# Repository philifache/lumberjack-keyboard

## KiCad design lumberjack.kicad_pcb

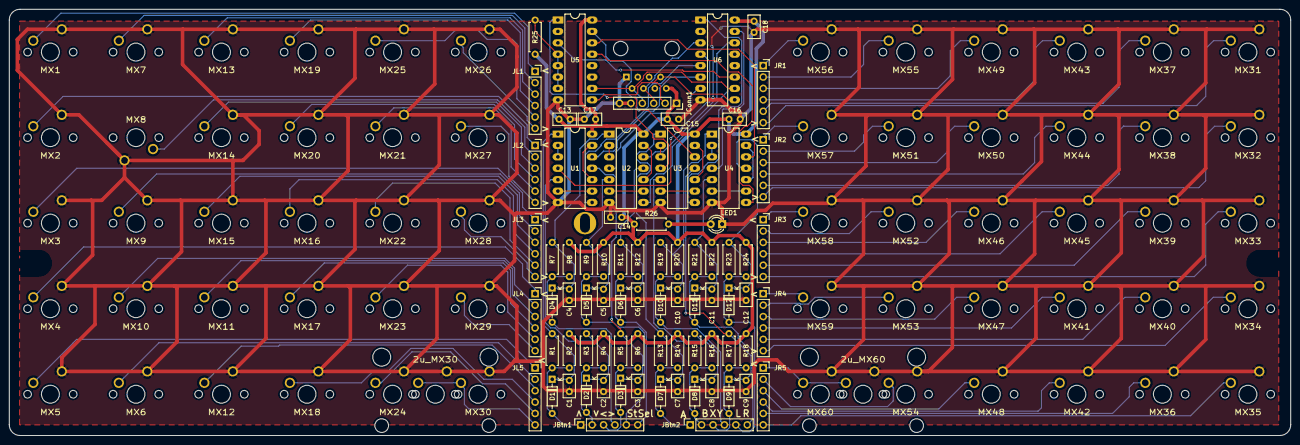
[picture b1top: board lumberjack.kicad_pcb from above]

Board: 2 copper layers, 285.4 x 94.9 mm, 142 parts (1 on the bottom side), 116 nets.

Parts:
2u_MX30, 2u_MX60: SW_Push; MX_PCB_200B
C1, C2, C3, C4, C5, C6, C7, C8, C9, C10, C11, C12, C13, C14, C15, C16, C17, C18: 0.1uF; C_Disc_D5.0mm_W2.5mm_P2.50mm
D1, D2, D3, D4, D5, D6, D7, D8, D9, D10, D11, D12: 1N4148; D_DO-35_SOD27_P7.62mm_Horizontal
H5, H6, H7: M2; MountingSlot_M2
J1: RJ45; RJ45_Amphenol_54602-x08_Horizontal
JBtn1, JBtn2: Conn_01x06_Male; PinSocket_1x06_P2.54mm_Vertical
JConn1: Conn_01x06_Male; PinSocket_1x06_P2.54mm_Vertical
JL1, JL2, JL3, JL4, JL5: Conn_01x06_Male; PinSocket_1x06_P2.54mm_Vertical
JR1, JR2, JR3, JR4, JR5: Conn_01x06_Male; PinSocket_1x06_P2.54mm_Vertical
LED1: RED; LED_D3.0mm
MX1, MX2, MX3, MX4, MX5, MX6, MX7, MX8, MX9, MX10, MX11, MX12, MX13, MX14, MX15, MX16, MX17, MX18, MX19, MX20, MX21, MX22, MX23, MX24, MX25, MX26, MX27, MX28, MX29, MX30, MX31, MX32, MX33, MX34, MX35, MX36, MX37, MX38, MX39, MX40, MX41, MX42, MX43, MX44, MX45, MX46, MX47, MX48, MX49, MX50, MX51, MX52, MX53, MX54, MX55, MX56, MX57, MX58, MX59, MX60: SW_Push; MX
R1, R3, R5, R7, R9, R11, R13, R15, R17, R19, R21, R23: 46.4k; R_Axial_DIN0207_L6.3mm_D2.5mm_P7.62mm_Horizontal
R2, R4, R6, R8, R10, R12, R14, R16, R18, R20, R22, R24, R25: 205k; R_Axial_DIN0207_L6.3mm_D2.5mm_P7.62mm_Horizontal
R26: 470; R_Axial_DIN0207_L6.3mm_D2.5mm_P7.62mm_Horizontal
U1, U2, U3, U4: 74HC14; DIP-14_W7.62mm_LongPads
U5, U6: 4021; DIP-16_W7.62mm_LongPads

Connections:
+5V: C13.1, C14.1, C15.1, C16.1, C17.1, C18.1, J1.8, JConn1.1, R2.1, R4.1, R6.1, R8.1, R10.1, R12.1, R14.1, R16.1, R18.1, R20.1, R22.1, R24.1, R25.1, R26.1, U1.14, U2.14, U3.14, U4.14, U5.16, U6.16
/BtnA: D7.2, JBtn2.1, R13.1, R14.2
/BtnADebounced: U3.4, U5.1
/BtnB: D8.2, JBtn2.2, R15.1, R16.2
/BtnBDebounced: U3.8, U6.1
/BtnDown: D2.2, JBtn1.2, R3.1, R4.2
/BtnDownDebounced: U1.8, U6.5
/BtnL: D12.2, JBtn2.5, R23.1, R24.2
/BtnLDebounced: U4.12, U5.14
/BtnLeft: D3.2, JBtn1.3, R5.1, R6.2
/BtnLeftDebounced: U1.12, U6.6
/BtnRDebounced: U4.8, U5.13
/BtnRight: D4.2, JBtn1.4, R7.1, R8.2
/BtnRightDebounced: U2.4, U6.7
/BtnSelect: D6.2, JBtn1.6, R11.1, R12.2
/BtnSelectDebounced: U2.12, U6.14
/BtnStart: D5.2, JBtn1.5, R9.1, R10.2
/BtnStartDebounced: U2.8, U6.13
/BtnUp: D1.2, JBtn1.1, R1.1, R2.2
/BtnUpDebounced: U1.4, U6.4
/BtnX: D9.2, JBtn2.3, R17.1, R18.2
/BtnXDebounced: U3.12, U5.15
/BtnY: D10.2, JBtn2.4, R19.1, R20.2
/BtnYDebounced: U4.4, U6.15
/L1.1: JL1.1, MX1.2
/L1.2: JL1.2, MX7.2
/L1.3: JL1.3, MX13.2
/L1.4: JL1.4, MX19.2
/L1.5: JL1.5, MX25.2
/L1.6: JL1.6, MX26.2
/L2.1: JL2.1, MX2.2
/L2.2: JL2.2, MX8.2
/L2.3: JL2.3, MX14.2
/L2.4: JL2.4, MX20.2
/L2.5: JL2.5, MX21.2
/L2.6: JL2.6, MX27.2
/L3.1: JL3.1, MX3.2
/L3.2: JL3.2, MX9.2
/L3.3: JL3.3, MX15.2
/L3.4: JL3.4, MX16.2
/L3.5: JL3.5, MX22.2
/L3.6: JL3.6, MX28.2
/L4.1: JL4.1, MX4.2
/L4.2: JL4.2, MX10.2
/L4.3: JL4.3, MX11.2
/L4.4: JL4.4, MX17.2
/L4.5: JL4.5, MX23.2
/L4.6: JL4.6, MX29.2
/L5.1: JL5.1, MX5.2
/L5.2: JL5.2, MX6.2
/L5.3: JL5.3, MX12.2
/L5.4: JL5.4, MX18.2
/L5.5: JL5.5, MX24.2
/L5.6: 2u_MX30.2, JL5.6, MX30.2
/R1.1: JR1.1, MX56.2
/R1.2: JR1.2, MX55.2
/R1.3: JR1.3, MX49.2
/R1.4: JR1.4, MX43.2
/R1.5: JR1.5, MX37.2
/R1.6: JR1.6, MX31.2
/R2.1: JR2.1, MX57.2
/R2.2: JR2.2, MX51.2
/R2.3: JR2.3, MX50.2
/R2.4: JR2.4, MX44.2
/R2.5: JR2.5, MX38.2
/R2.6: JR2.6, MX32.2
/R3.1: JR3.1, MX58.2
/R3.2: JR3.2, MX52.2
/R3.3: JR3.3, MX46.2
/R3.4: JR3.4, MX45.2
/R3.5: JR3.5, MX39.2
/R3.6: JR3.6, MX33.2
/R4.1: JR4.1, MX59.2
/R4.2: JR4.2, MX53.2
/R4.3: JR4.3, MX47.2
/R4.4: JR4.4, MX41.2
/R4.5: JR4.5, MX40.2
/R4.6: JR4.6, MX34.2
/R5.1: 2u_MX60.2, JR5.1, MX60.2
/R5.2: JR5.2, MX54.2
/R5.3: JR5.3, MX48.2
/R5.4: JR5.4, MX42.2
/R5.5: JR5.5, MX36.2
/R5.6: JR5.6, MX35.2
/RtnR: D11.2, JBtn2.6, R21.1, R22.2
/clock: J1.2, JConn1.4, U5.10, U6.10
/data: J1.4, JConn1.3, U6.3
/reset: J1.7, JConn1.2, U5.9, U6.9
GND: 2u_MX30.1, 2u_MX60.1, C1.2, C2.2, C3.2, C4.2, C5.2, C6.2, C7.2, C8.2, C9.2, C10.2, C11.2, C12.2, C13.2, C14.2, C15.2, C16.2, C17.2, C18.2, J1.1, JConn1.5, JConn1.6, LED1.1, MX1.1, MX2.1, MX3.1, MX4.1, MX5.1, MX6.1, MX7.1, MX8.1, MX9.1, MX10.1, MX11.1, MX12.1, MX13.1, MX14.1, MX15.1, MX16.1, MX17.1, MX18.1, MX19.1, MX20.1, MX21.1, MX22.1, MX23.1, MX24.1, MX25.1, MX26.1, MX27.1, MX28.1, MX29.1, MX30.1, MX31.1, MX32.1, MX33.1, MX34.1, MX35.1, MX36.1, MX37.1, MX38.1, MX39.1, MX40.1, MX41.1, MX42.1, MX43.1, MX44.1, MX45.1, MX46.1, MX47.1, MX48.1, MX49.1, MX50.1, MX51.1, MX52.1, MX53.1, MX54.1, MX55.1, MX56.1, MX57.1, MX58.1, MX59.1, MX60.1, U1.7, U2.7, U3.7, U4.7, U5.8, U6.8
unnamed: C1.1, D1.1, R1.2, U1.1
unnamed: C2.1, D2.1, R3.2, U1.5
unnamed: C3.1, D3.1, R5.2, U1.11
unnamed: C4.1, D4.1, R7.2, U2.1
unnamed: C5.1, D5.1, R9.2, U2.5
unnamed: C6.1, D6.1, R11.2, U2.11
unnamed: C7.1, D7.1, R13.2, U3.1
unnamed: C8.1, D8.1, R15.2, U3.5
unnamed: C9.1, D9.1, R17.2, U3.11
unnamed: C10.1, D10.1, R19.2, U4.1
unnamed: C11.1, D11.1, R21.2, U4.5
unnamed: C12.1, D12.1, R23.2, U4.11
unnamed: LED1.2, R26.2
unnamed: R25.2, U5.4, U5.5, U5.6, U5.7
unnamed: U1.2, U1.3
unnamed: U1.6, U1.9
unnamed: U1.10, U1.13
unnamed: U2.2, U2.3
unnamed: U2.6, U2.9
unnamed: U2.10, U2.13
unnamed: U3.2, U3.3
unnamed: U3.6, U3.9
unnamed: U3.10, U3.13
unnamed: U4.2, U4.3
unnamed: U4.6, U4.9
unnamed: U4.10, U4.13
unnamed: U5.3, U6.11

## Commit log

2021-08-09 Update lumberjack.sch
    Changed Schematic to SNES
2021-08-09 Update lumberjack.kicad_pcb
    Updated PCB file, removed all traces
2021-08-11 Update lumberjack.sch
    Update schematic, added debounce circuits (not done, need to calculate resistors). Is it the last thing to do?
2021-08-11 Update lumberjack.sch
    Some descriptions and calculations
2021-08-12 Update lumberjack.sch
    End of the schematic? Maybe I'll add a couple of headers if there's space.
2021-08-12 Update lumberjack.sch
    Needed a couple of packages, will need to go surface mount, we do not have that much space. R100 needs to be calculated.
2021-08-13 Update lumberjack.sch
    Schematic fix
2021-08-13 Update lumberjack.kicad_pcb
    PCB before infill
2021-08-13 Couple 'o rule fixes
2021-08-13 Ready for a ground plane? 2
2021-08-13 Couple of wires on the wrong side
2021-08-13 With filled ground
2021-08-14 Finished V1 PCB?
